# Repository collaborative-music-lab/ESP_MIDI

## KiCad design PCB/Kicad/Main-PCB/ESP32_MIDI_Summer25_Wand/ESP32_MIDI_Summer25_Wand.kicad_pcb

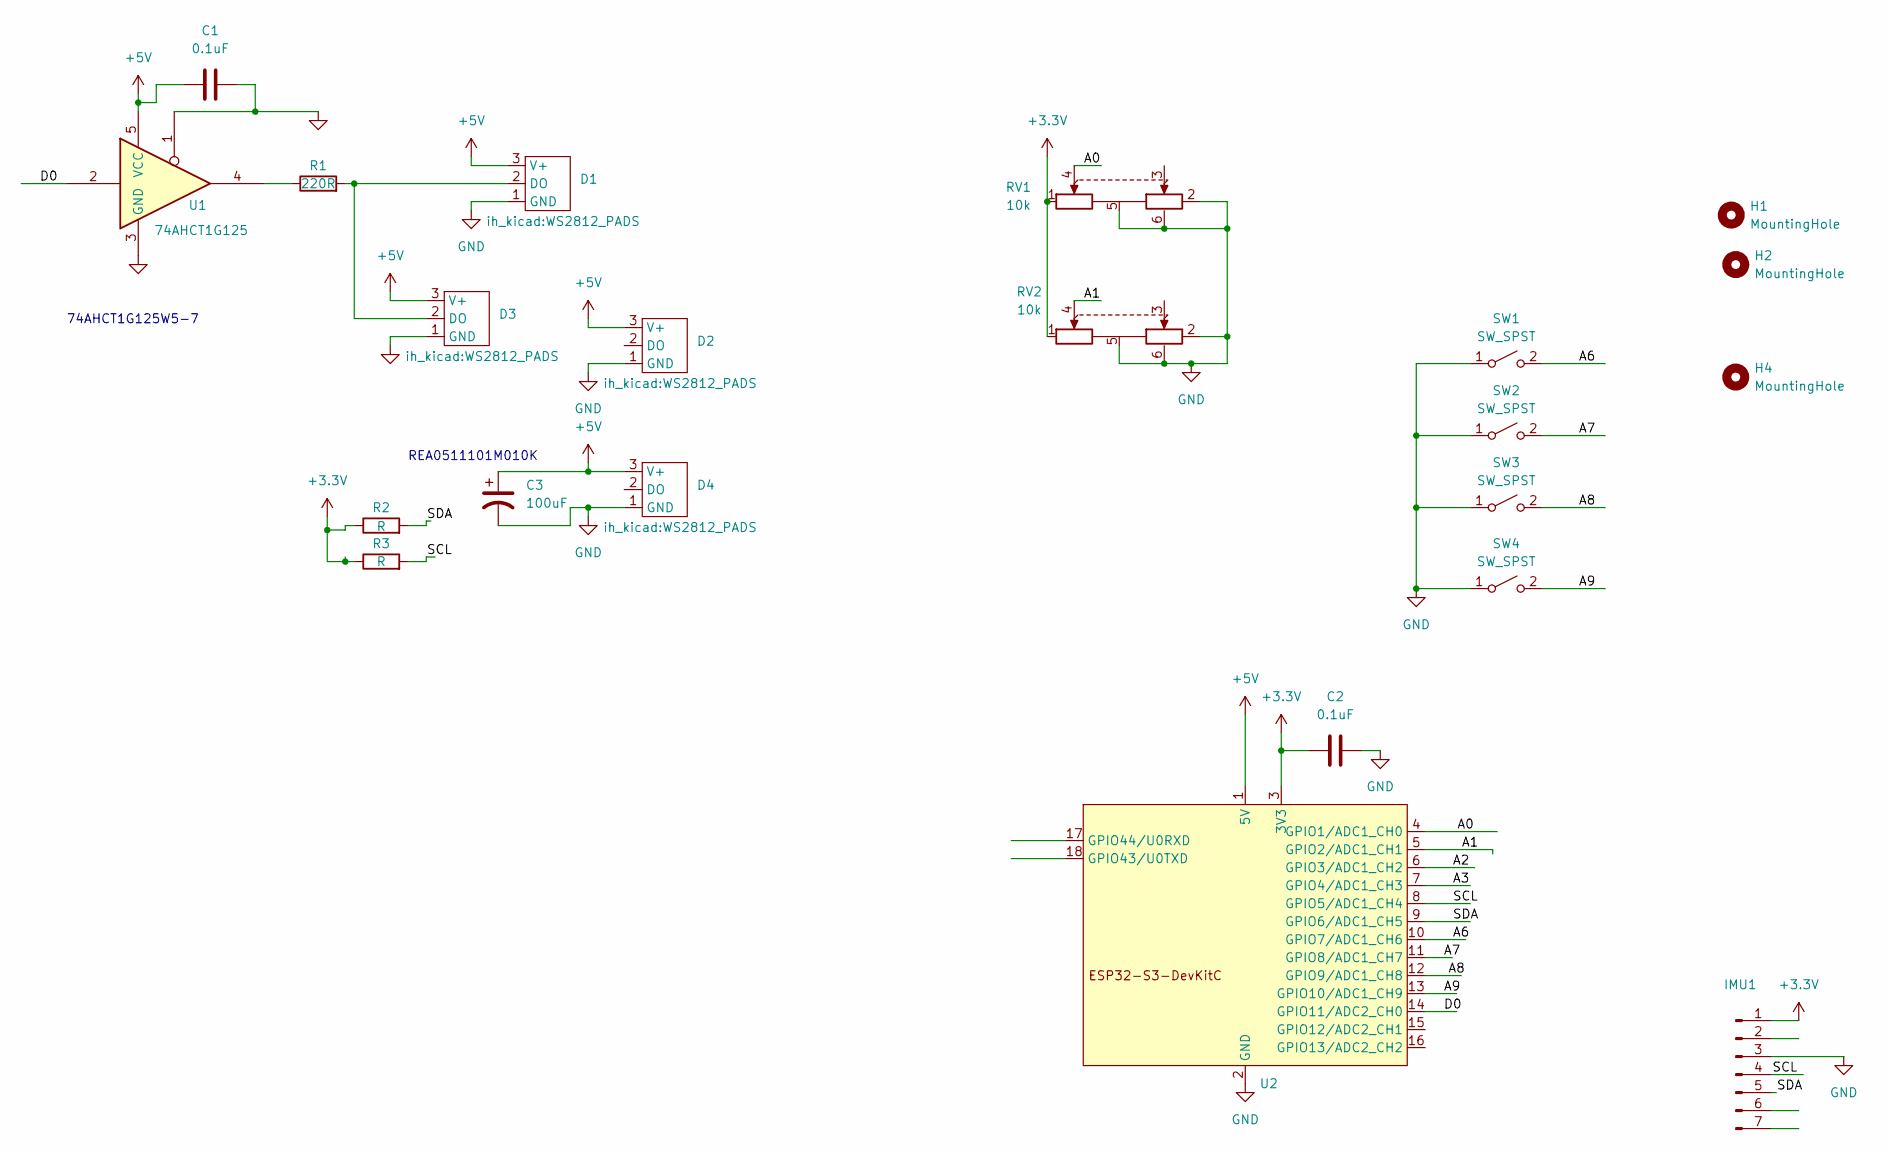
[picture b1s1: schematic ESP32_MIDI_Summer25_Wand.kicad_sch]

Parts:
C1, C2: 0.1uF; C_Disc_D5.1mm_W3.2mm_P5.00mm
C3: 100uF; CP_Radial_D5.0mm_P2.00mm
D1, D2, D3, D4: WS2812_PADS
H1, H2, H4: MountingHole; MountingHole_3.2mm_M3
IMU1: Conn_01x07_Pin; PinHeader_1x07_P2.54mm_Vertical
R1: 220R; R_Axial_DIN0204_L3.6mm_D1.6mm_P7.62mm_Horizontal
R2, R3: R; R_Axial_DIN0204_L3.6mm_D1.6mm_P7.62mm_Horizontal
RV1, RV2: 10k; potentiometer_wheel_10mm_SMD-shield
SW1, SW2, SW3, SW4: SW_SPST; SW_Cherry_MX_1.00u_PCB
U1: 74AHCT1G125; TSOT-23-5_HandSoldering
U2: Wifiduino-ESP32S3-SMD

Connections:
+3.3V: C2.2, IMU1.1, R2.1, R3.1, RV1.1 (1A), RV2.1 (1A), U2.3 (3V3)
+5V: C1.1, C3.1, D1.3 (V+), D2.3 (V+), D3.3 (V+), D4.3 (V+), U1.5 (VCC), U2.1 (5V)
/A0: RV1.4 (1-Wiper), U2.4 (GPIO1/ADC1_CH0)
/A1: RV2.4 (1-Wiper), U2.5 (GPIO2/ADC1_CH1)
/A2: U2.6 (GPIO3/ADC1_CH2)
/A3: U2.7 (GPIO4/ADC1_CH3)
/A6: SW1.2 (B), U2.10 (GPIO7/ADC1_CH6)
/A7: SW2.2 (B), U2.11 (GPIO8/ADC1_CH7)
/A8: SW3.2 (B), U2.12 (GPIO9/ADC1_CH8)
/A9: SW4.2 (B), U2.13 (GPIO10/ADC1_CH9)
/D0: U1.2, U2.14 (GPIO11/ADC2_CH0)
/SCL: IMU1.4, R3.2, U2.8 (GPIO5/ADC1_CH4)
/SDA: IMU1.5, R2.2, U2.9 (GPIO6/ADC1_CH5)
GND: C1.2, C2.1, C3.2, D1.1 (GND), D2.1 (GND), D3.1 (GND), D4.1 (GND), IMU1.3, RV1.2 (2B), RV1.5 (Common), RV1.6 (Shield), RV2.2 (2B), RV2.5 (Common), RV2.6 (Shield), SW1.1 (A), SW2.1 (A), SW3.1 (A), SW4.1 (A), U1.1, U1.3 (GND), U2.2 (GND)
unnamed: D1.2 (DO), D3.2 (DO), R1.2
unnamed: R1.1, U1.4

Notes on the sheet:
REA0511101M010K
74AHCT1G125W5-7

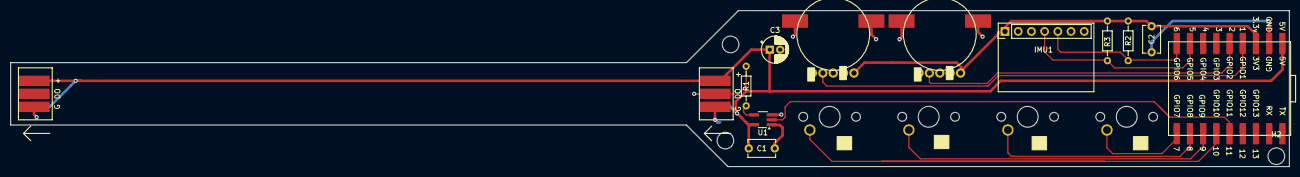
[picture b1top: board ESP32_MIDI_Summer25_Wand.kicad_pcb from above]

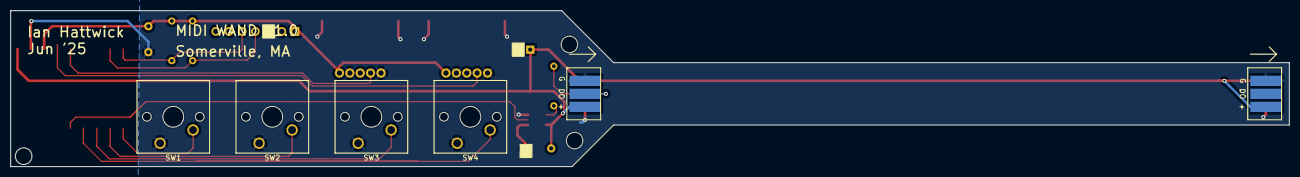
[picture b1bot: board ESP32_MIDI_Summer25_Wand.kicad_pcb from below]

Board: 2 copper layers, 246.0 x 30.0 mm, 22 parts (6 on the bottom side), 14 nets.

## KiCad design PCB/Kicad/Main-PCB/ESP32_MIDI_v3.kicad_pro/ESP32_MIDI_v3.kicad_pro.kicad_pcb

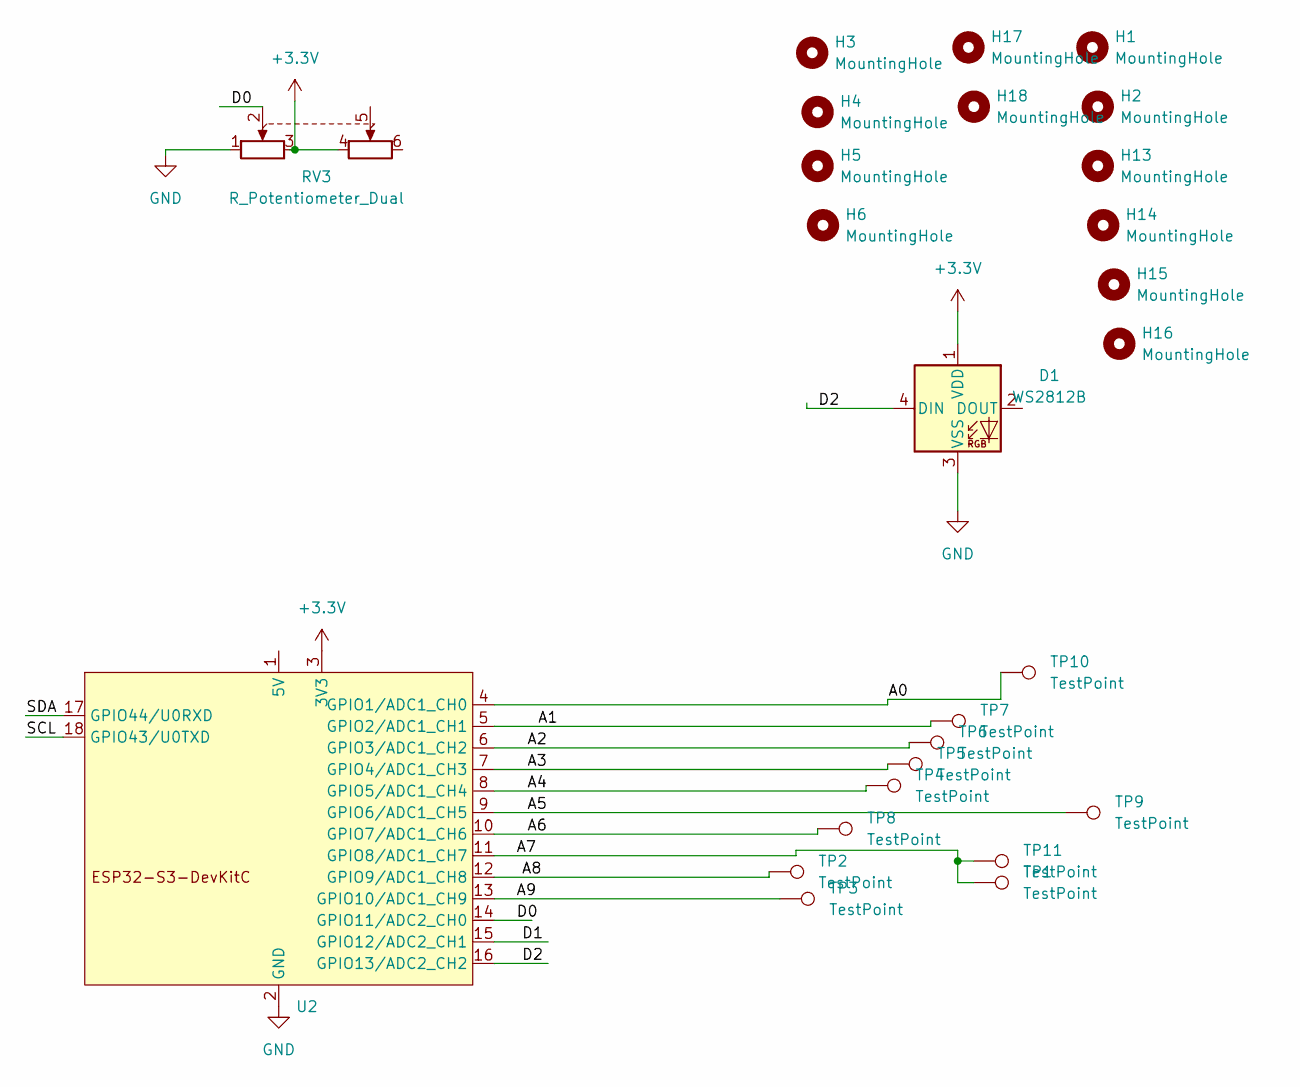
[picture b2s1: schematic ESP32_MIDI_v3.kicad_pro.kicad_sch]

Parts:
D1: WS2812B; LED_D5.0mm-4_RGB_Wide_Pins
H1, H2, H3, H4, H5, H6, H13, H14, H15, H16, H17, H18: MountingHole; MountingHole_3.2mm_M3
RV3: R_Potentiometer_Dual; potentiometer_wheel_16mm
TP1, TP2, TP3, TP4, TP5, TP6, TP7, TP10: TestPoint; recorder-touchpad
TP8, TP9: TestPoint; recorder-touchtrack
TP11: TestPoint; recorder-touchpad-narrow
U2: Wifiduino-ESP32S3-SMD

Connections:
+3.3V: D1.1 (VDD), RV3.3, RV3.4, U2.3 (3V3)
/A0: TP10.1, U2.4 (GPIO1/ADC1_CH0)
/A1: TP7.1, U2.5 (GPIO2/ADC1_CH1)
/A2: TP6.1, U2.6 (GPIO3/ADC1_CH2)
/A3: TP5.1, U2.7 (GPIO4/ADC1_CH3)
/A4: TP4.1, U2.8 (GPIO5/ADC1_CH4)
/A5: TP9.1, U2.9 (GPIO6/ADC1_CH5)
/A6: TP8.1, U2.10 (GPIO7/ADC1_CH6)
/A7: TP1.1, TP11.1, U2.11 (GPIO8/ADC1_CH7)
/A8: TP2.1, U2.12 (GPIO9/ADC1_CH8)
/A9: TP3.1, U2.13 (GPIO10/ADC1_CH9)
/D0: RV3.2, U2.14 (GPIO11/ADC2_CH0)
/D1: U2.15 (GPIO12/ADC2_CH1)
/D2: D1.4 (DIN), U2.16 (GPIO13/ADC2_CH2)
/SCL: U2.18 (GPIO43/U0TXD)
/SDA: U2.17 (GPIO44/U0RXD)
GND: D1.3 (VSS), RV3.1, U2.2 (GND)

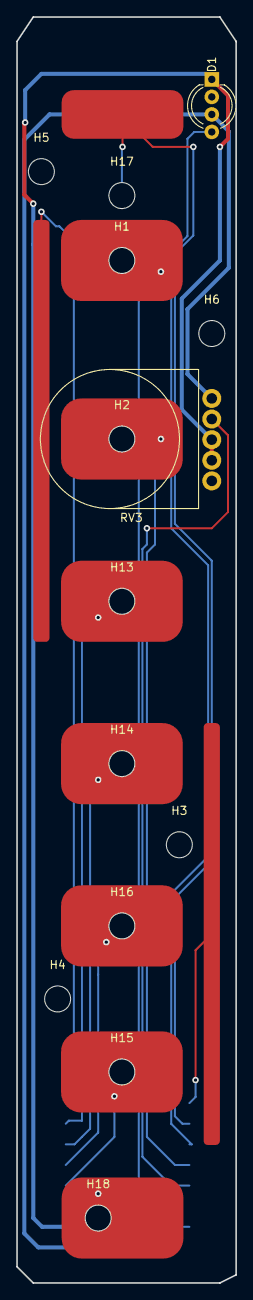
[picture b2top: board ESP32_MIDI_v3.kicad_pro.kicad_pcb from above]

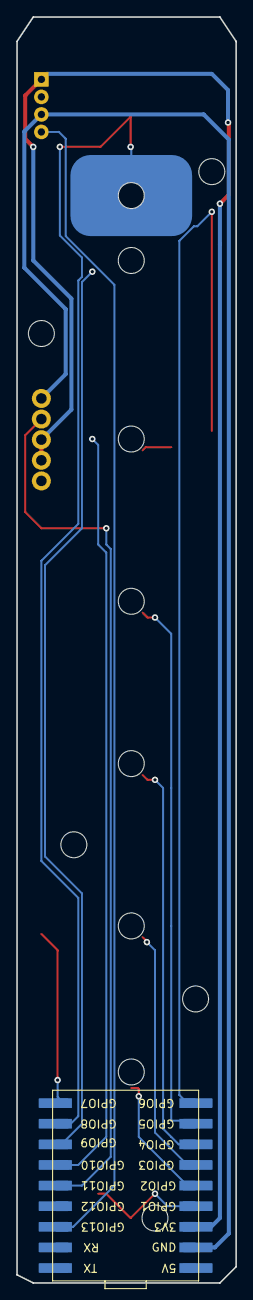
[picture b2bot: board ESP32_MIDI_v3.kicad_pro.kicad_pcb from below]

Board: 2 copper layers, 27.0 x 156.0 mm, 26 parts (2 on the bottom side), 14 nets.

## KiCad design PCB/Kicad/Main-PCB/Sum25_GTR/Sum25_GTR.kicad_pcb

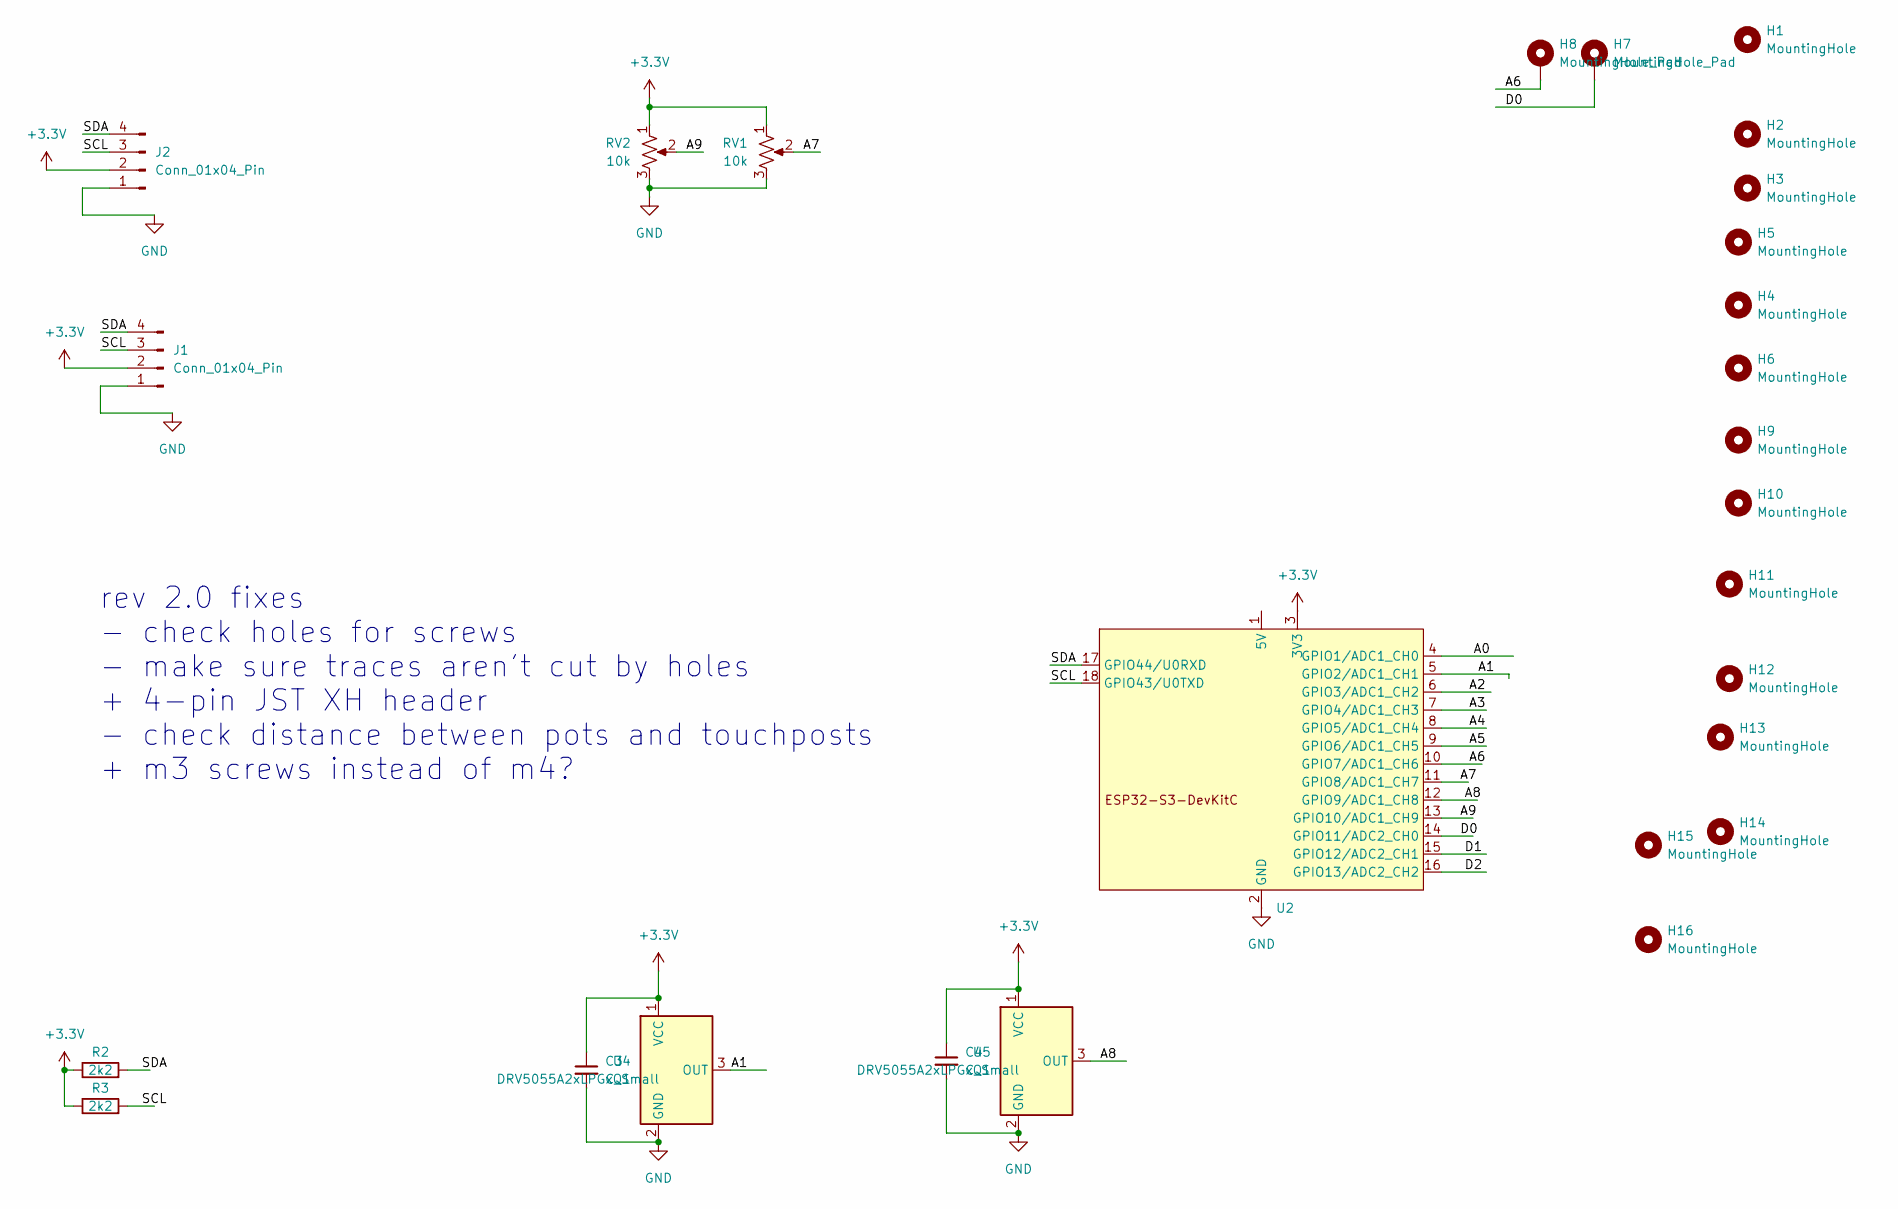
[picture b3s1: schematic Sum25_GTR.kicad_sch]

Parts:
C3, C4: C_Small; C_Disc_D6.0mm_W2.5mm_P5.00mm
H1, H2, H3, H4, H5, H6, H9, H10, H11, H12, H13, H14, H15, H16: MountingHole; MountingHole_3.2mm_M3
H7, H8: MountingHole_Pad; MountingHole_6.4mm_M6_DIN965_Pad_TopBottom
J1, J2: Conn_01x04_Pin; PinSocket_1x04_P2.54mm_Vertical
R2, R3: 2k2; R_Axial_DIN0204_L3.6mm_D1.6mm_P7.62mm_Horizontal
RV1, RV2: 10k; Potentiometer_Alps_RK09K_Single_Vertical
U2: Wifiduino-ESP32S3-SMD
U4, U5: DRV5055A2xLPGxQ1; TO-92_flat

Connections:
+3.3V: C3.1, C4.1, J1.2, J2.2, R2.1, R3.1, RV1.1, RV2.1, U2.3 (3V3), U4.1 (VCC), U5.1 (VCC)
/A0: U2.4 (GPIO1/ADC1_CH0)
/A1: U2.5 (GPIO2/ADC1_CH1), U4.3 (OUT)
/A2: U2.6 (GPIO3/ADC1_CH2)
/A3: U2.7 (GPIO4/ADC1_CH3)
/A4: U2.8 (GPIO5/ADC1_CH4)
/A5: U2.9 (GPIO6/ADC1_CH5)
/A6: H8.1, U2.10 (GPIO7/ADC1_CH6)
/A7: RV1.2, U2.11 (GPIO8/ADC1_CH7)
/A8: U2.12 (GPIO9/ADC1_CH8), U5.3 (OUT)
/A9: RV2.2, U2.13 (GPIO10/ADC1_CH9)
/D0: H7.1, U2.14 (GPIO11/ADC2_CH0)
/D1: U2.15 (GPIO12/ADC2_CH1)
/D2: U2.16 (GPIO13/ADC2_CH2)
/SCL: J1.3, J2.3, R3.2, U2.18 (GPIO43/U0TXD)
/SDA: J1.4, J2.4, R2.2, U2.17 (GPIO44/U0RXD)
GND: C3.2, C4.2, J1.1, J2.1, RV1.3, RV2.3, U2.2 (GND), U4.2 (GND), U5.2 (GND)

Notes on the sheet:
rev 2.0 fixes - check holes for screws - make sure traces aren't cut by holes + 4-pin JST XH header - check distance between pots and touchposts + m3 screws instead of m4?

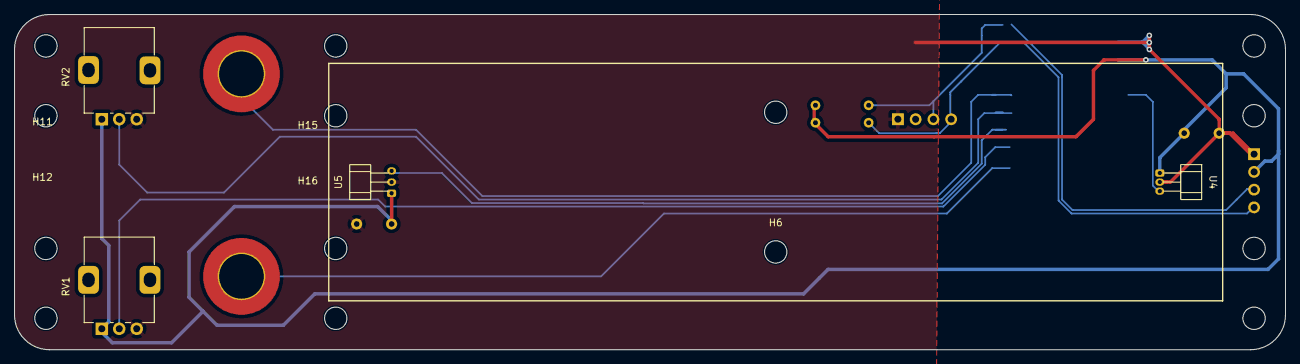
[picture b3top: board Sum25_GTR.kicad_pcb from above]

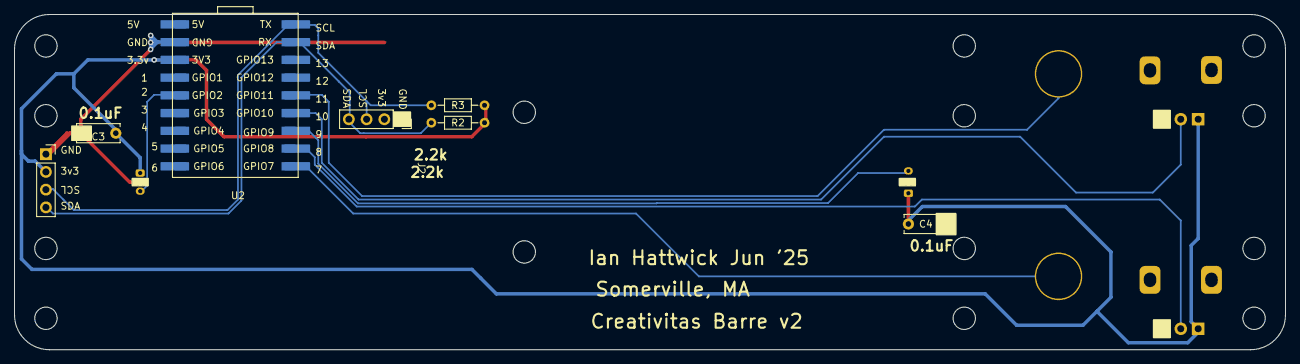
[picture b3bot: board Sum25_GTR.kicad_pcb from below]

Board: 2 copper layers, 182.0 x 48.0 mm, 27 parts (7 on the bottom side), 10 nets.
